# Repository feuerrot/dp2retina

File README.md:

# dp2retina

Nach [diesem Blogpost](http://emerythacks.blogspot.de/2013/04/connecting-ipad-retina-lcd-to-pc.html) und Displaydatenblatt gebaut: Ein passiver Adapter von Displayport auf embedded Displayport.
Zusätzlich: zwei MAX17129 für die 12 Kanäle der Hintergrundbeleuchtung + ein ATTiny45 mit VUSB-Support für HintergrundbeleuchtungsPWM.

## Projektstatus
Das Platinenlayout funktioniert. Der Connector für das Display ist nicht schön zu löten und die Schaltreglerkomponenten mittels Lötkolben auch nicht so.

## Todo
* größere Platine
 * seitliche Anschlüsse
 * Buttons zur Helligkeitsregelung
* ein Gehäuse
 * 3D-Druck ist zu klein -> Lasercutter&Plexiglas?

## Layout und so

### Schaltplan

### Layout

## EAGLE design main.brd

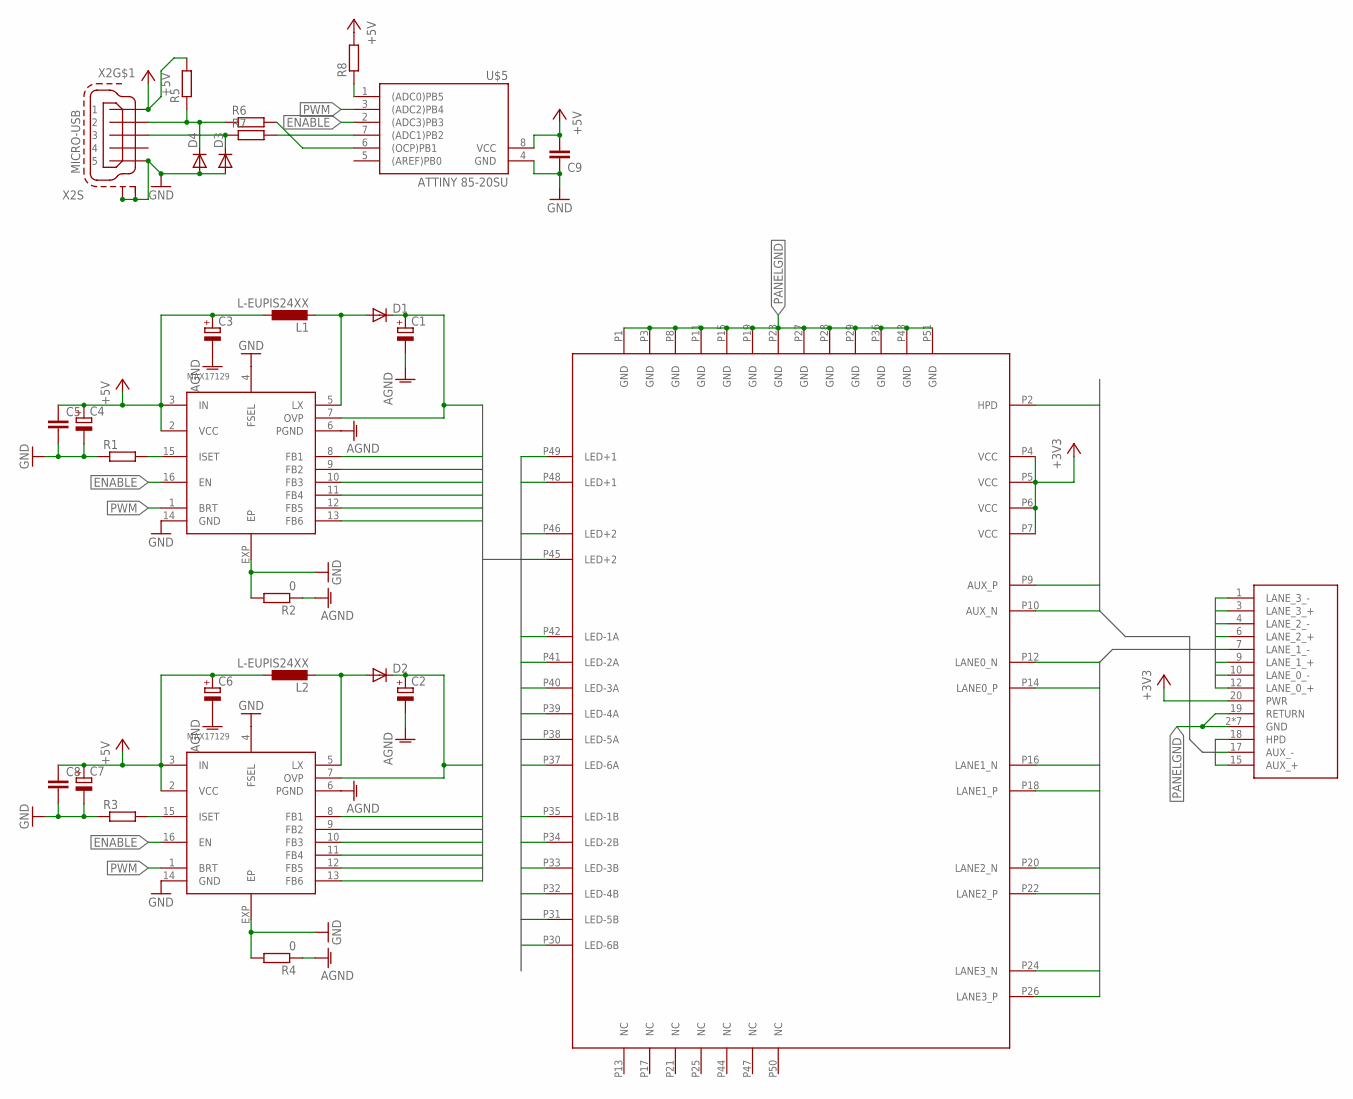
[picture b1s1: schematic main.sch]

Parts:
C1, C2, C3, C4, C6, C7: CPOL-EUB; PANASONIC_B
C5, C8, C9: C-EUC0805; C0805
D1, D2: DIODE-DO214AA; DO214AA
D3, D4: DIODE-MINIMELF; MINIMELF
L1, L2: L-EUPIS24XX; PIS24XX
R1, R3: R-EU_M0805; M0805
R2, R4: 0; R0201
R5, R6, R7, R8: R-EU_R0805; R0805
U$1: IPAD3-CONN; MOLEX502250-5191
U$2: DP1R020JQ1SINK; DP1R020JQ1
U$3, U$4: MAX17129; QFN16-4X4
U$5: ATTINY 85-20SU; SOIC8
X2: MICRO-USB; SMD

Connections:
+3V3: U$1.P4 (VCC), U$1.P5 (VCC), U$1.P6 (VCC), U$1.P7 (VCC), U$2.20 (PWR)
AGND: C1.-, C2.-, C3.-, C6.-, R2.1, R4.1, U$3.6 (PGND), U$4.6 (PGND)
AUX_N: U$1.P10 (AUX_N), U$2.17 (AUX_-)
AUX_P: U$1.P9 (AUX_P), U$2.15 (AUX_+)
ENABLE: U$3.16 (EN), U$4.16 (EN), U$5.2 ((ADC3)PB3)
HPD: U$1.P2 (HPD), U$2.18 (HPD)
LANE0_N: U$1.P12 (LANE0_N), U$2.10 (LANE_0_-)
LANE0_P: U$1.P14 (LANE0_P), U$2.12 (LANE_0_+)
LANE1_N: U$1.P16 (LANE1_N), U$2.7 (LANE_1_-)
LANE1_P: U$1.P18 (LANE1_P), U$2.9 (LANE_1_+)
LANE2_N: U$1.P20 (LANE2_N), U$2.4 (LANE_2_-)
LANE2_P: U$1.P22 (LANE2_P), U$2.6 (LANE_2_+)
LANE3_N: U$1.P24 (LANE3_N), U$2.1 (LANE_3_-)
LANE3_P: U$1.P26 (LANE3_P), U$2.3 (LANE_3_+)
LED_N_A_1: U$1.P42 (LED-1A), U$3.8 (FB1)
LED_N_A_2: U$1.P41 (LED-2A), U$3.11 (FB4)
LED_N_A_3: U$1.P40 (LED-3A), U$3.9 (FB2)
LED_N_A_4: U$1.P39 (LED-4A), U$3.12 (FB5)
LED_N_A_5: U$1.P38 (LED-5A), U$3.10 (FB3)
LED_N_A_6: U$1.P37 (LED-6A), U$3.13 (FB6)
LED_N_B_1: U$1.P35 (LED-1B), U$4.8 (FB1)
LED_N_B_2: U$1.P34 (LED-2B), U$4.11 (FB4)
LED_N_B_3: U$1.P33 (LED-3B), U$4.9 (FB2)
LED_N_B_4: U$1.P32 (LED-4B), U$4.12 (FB5)
LED_N_B_5: U$1.P31 (LED-5B), U$4.10 (FB3)
LED_N_B_6: U$1.P30 (LED-6B), U$4.13 (FB6)
LED_P_1: C1.+, D1.C, U$1.P48 (LED+1), U$1.P49 (LED+1), U$3.7 (OVP)
LED_P_2: C2.+, D2.C, U$1.P45 (LED+2), U$1.P46 (LED+2), U$4.7 (OVP)
unnamed: R1.2, U$3.15 (ISET)
unnamed: R3.2, U$4.15 (ISET)
unnamed: D1.A, L1.1 (2), U$3.5 (LX)
unnamed: D2.A, L2.1 (2), U$4.5 (LX)
unnamed: R6.2, U$5.6 ((OCP)PB1)
unnamed: R7.2, U$5.7 ((ADC1)PB2)
unnamed 36: D3.C, R7.1, X2.3; also elsewhere on the board
unnamed 37: D4.C, R5.1, R6.1, X2.2; also elsewhere on the board
unnamed: R8.1, U$5.1 ((ADC0)PB5)
PANELGND: U$1.P1 (GND), U$1.P3 (GND), U$1.P8 (GND), U$1.P11 (GND), U$1.P15 (GND), U$1.P19 (GND), U$1.P23 (GND), U$1.P27 (GND), U$1.P28 (GND), U$1.P29 (GND), U$1.P36 (GND), U$1.P43 (GND), U$1.P51 (GND), U$2.2 (GND), U$2.5 (GND), U$2.8 (GND), U$2.11 (GND), U$2.13 (GND), U$2.14 (GND), U$2.16 (GND), U$2.19 (RETURN)
PWM: U$3.1 (BRT), U$4.1 (BRT), U$5.3 ((ADC2)PB4)

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
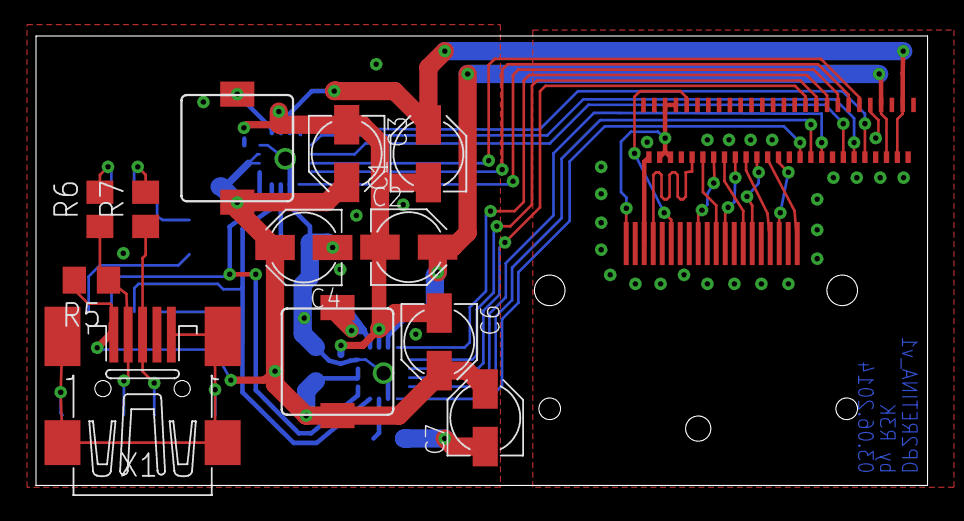
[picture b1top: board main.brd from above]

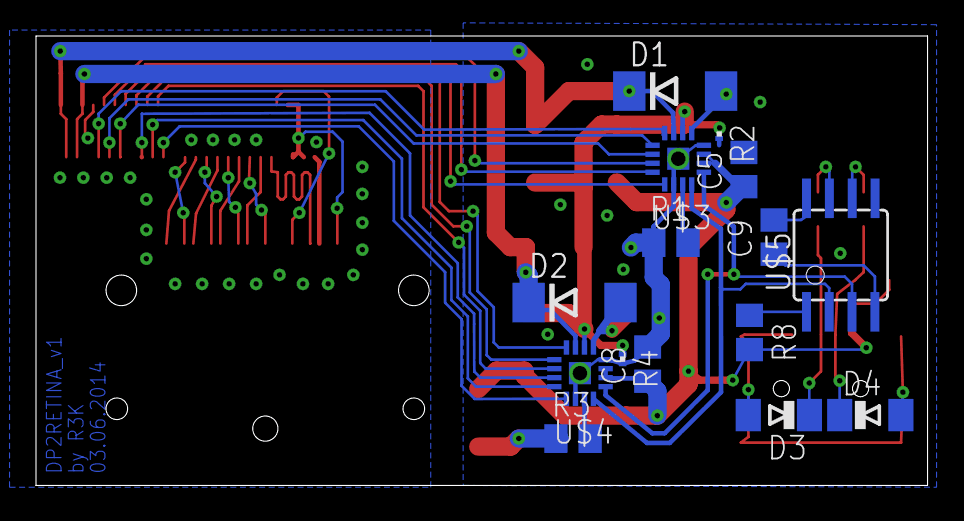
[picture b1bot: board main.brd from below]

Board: 2 copper layers, 49.5 x 25.0 mm, 29 parts (15 on the bottom side), 43 nets.

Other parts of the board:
X1: USB; 32005-201

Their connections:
unnamed 36: X1.3; also elsewhere on the board
unnamed 37: X1.2; also elsewhere on the board

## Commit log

2015-06-27 add readme + images
2015-06-27 bigger image of the board
